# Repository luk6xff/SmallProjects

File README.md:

# SmallProjects
Here you can find some of my old tiny projects, code snippets, made for tests, fun or university which were created veeery long time ago :)

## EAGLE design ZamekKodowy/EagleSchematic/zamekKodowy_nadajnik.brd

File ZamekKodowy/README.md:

Digital wireless radio transmitter/receiver. TX consists of a 4x4 keyboard that can be used to type a PIN Code and then , the proper generated frame  is being sent to the specified receiver, All PIN codes are stored in non volatile EEPROM memory both in the transmiter and receiver. The device was made using STM32F051R8T6 microntroller , nRF24L01+ radio transceivers, AT24C64D eeprom memory . The entire system is powered by the FREERTOS

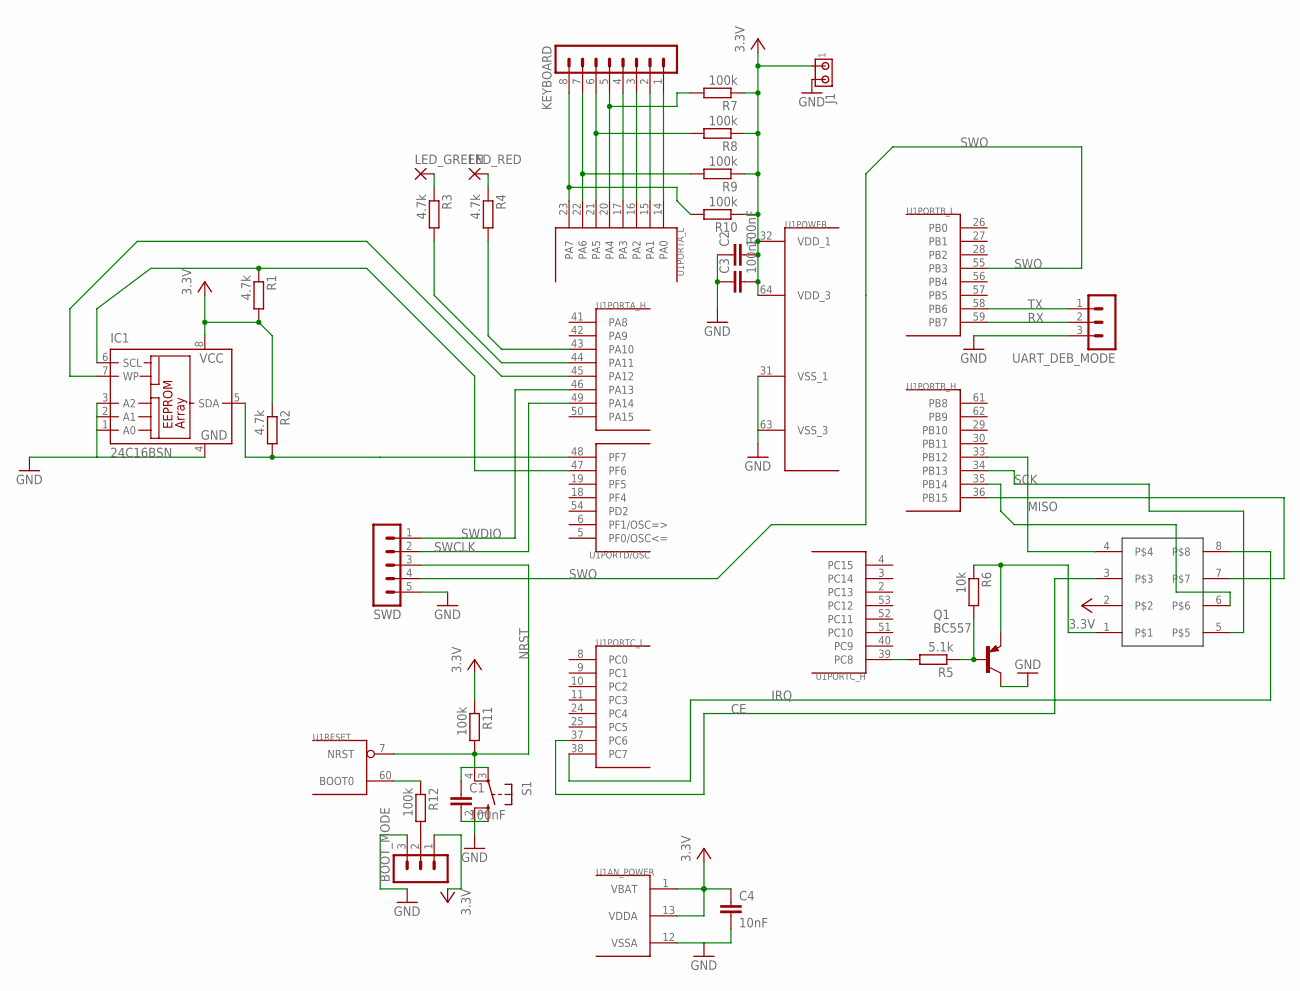
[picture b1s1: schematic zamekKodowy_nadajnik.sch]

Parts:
BOOT_MODE: MA03-1
C1, C2, C3: 100nF; C0603
C4: 10nF; C0603
CON1: CON10
IC1: 24C16BSN; SO-08
J1: MTA02-100; 10X02MTA
KEYBOARD: MA08-1
LED_GREEN: 2,54/0,9
LED_RED: 2,54/0,9
Q1: BC557; TO92
R1, R2, R3, R4: 4.7k; R0603
R5: 5.1k; R0603
R6: 10k; R0603
R7, R8, R9, R10, R11, R12: 100k; R0603
S1: 10-XX; B3F-10XX
SWD: MA05-1
U1: STM32F10XRXT6; TQFP64
UART_DEB_MODE: MA03-1

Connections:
CE: CON1.3, U1.37 (PC6)
GND: BOOT_MODE.3, C1.2, C2.1, C3.1, C4.2, IC1.1 (A0), IC1.2 (A1), IC1.3 (A2), IC1.4 (GND), J1.2, Q1.3 (C), S1.1 (S), S1.2 (S1), SWD.5, U1.12 (VSSA), U1.31 (VSS_1), U1.63 (VSS_3), UART_DEB_MODE.3
IRQ: CON1.8, U1.38 (PC7)
MISO: CON1.7, U1.36 (PB15)
MOSI: CON1.6, U1.35 (PB14)
unnamed: IC1.5 (SDA), R2.2, U1.48 (PF7)
unnamed: IC1.6 (SCL), R1.1, U1.47 (PF6)
unnamed: IC1.7 (WP), U1.45 (PA12)
unnamed: R3.2, U1.44 (PA11)
unnamed: R4.2, U1.43 (PA10)
unnamed: LED_GREEN.1, R3.1
unnamed: LED_RED.1, R4.1
unnamed: Q1.2 (B), R5.1, R6.2
unnamed: KEYBOARD.8, R10.2, U1.23 (PA7)
unnamed: R5.2, U1.39 (PC8)
unnamed: CON1.1, Q1.1 (E), R6.1
unnamed: KEYBOARD.7, R9.2, U1.22 (PA6)
unnamed: KEYBOARD.6, R8.2, U1.21 (PA5)
unnamed: KEYBOARD.5, R7.2, U1.20 (PA4)
unnamed: KEYBOARD.4, U1.17 (PA3)
unnamed: KEYBOARD.3, U1.16 (PA2)
unnamed: KEYBOARD.2, U1.15 (PA1)
unnamed: KEYBOARD.1, U1.14 (PA0)
unnamed: R12.1, U1.60 (BOOT0)
unnamed: BOOT_MODE.2, R12.2
NRST: C1.1, R11.2, S1.3, S1.4 (P1), SWD.3, U1.7 (NRST)
NSS: CON1.4, U1.33 (PB12)
RX: U1.59 (PB7), UART_DEB_MODE.2
SCK: CON1.5, U1.34 (PB13)
SWCLK: SWD.2, U1.49 (PA14)
SWDIO: SWD.1, U1.46 (PA13)
SWO: SWD.4, U1.55 (PB3)
TX: U1.58 (PB6), UART_DEB_MODE.1
VCC: BOOT_MODE.1, C2.2, C3.2, C4.1, CON1.2, IC1.8 (VCC), J1.1, R1.2, R2.1, R7.1, R8.1, R9.1, R10.1, R11.1, U1.1 (VBAT), U1.13 (VDDA), U1.32 (VDD_1), U1.64 (VDD_3)

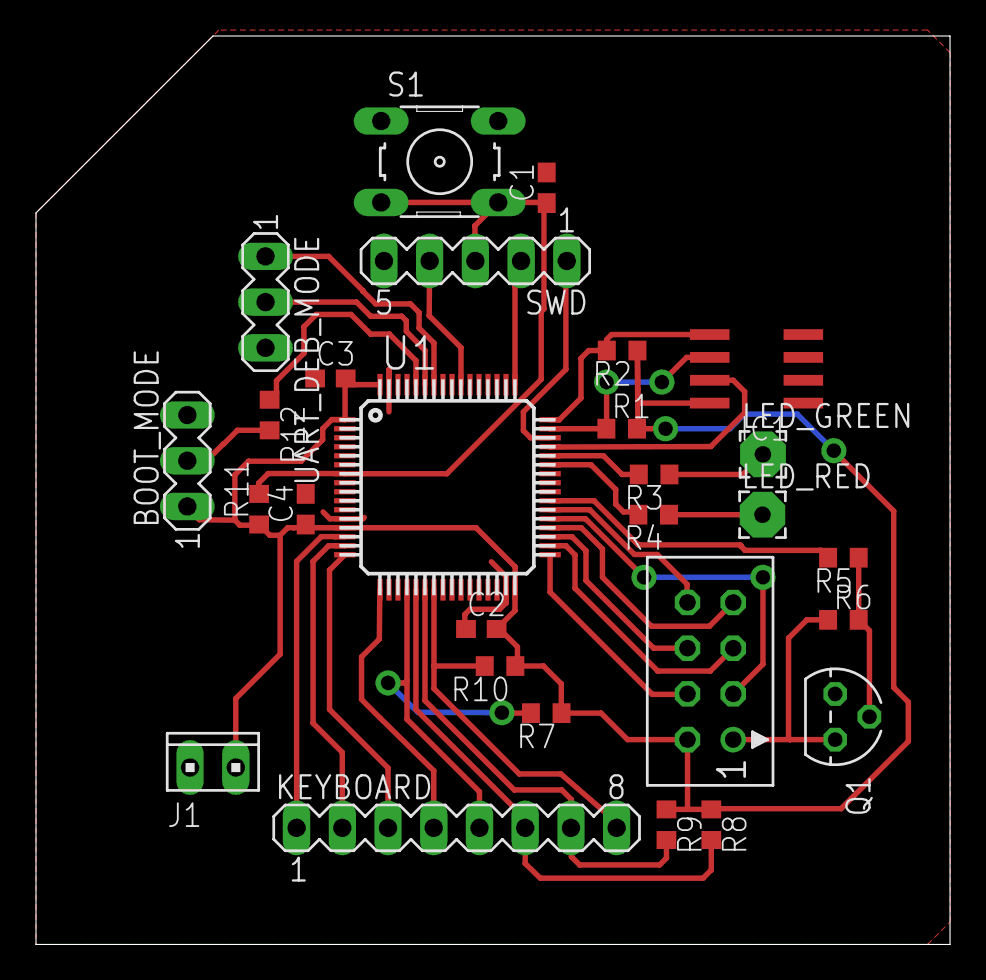
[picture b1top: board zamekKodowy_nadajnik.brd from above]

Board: 2 copper layers, 50.8 x 50.5 mm, 28 parts (0 on the bottom side), 34 nets.

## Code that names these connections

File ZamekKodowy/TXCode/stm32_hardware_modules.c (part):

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/**
 *@name void SPI2_For_NRF24L01_init(void)
 *@brief Initialization of the required SPI2 module registers
 *@brief PINOUT:  PB12(SPI2_NSS),  PB13(SPI2_SCK),  PB14(SPI2_MISO),  PB15(SPI2_MOSI)
 *@param NONE
 *@retval NONE
 *
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// GPIO
	//SetEnabledNRF24L01();
	GPIOB->MODER |= GPIO_MODER_MODER13_1 | GPIO_MODER_MODER14_1
			| GPIO_MODER_MODER15_1; // PB13(SPI2_SCK) , PB14(SPI2_MISO) , PB15(SPI2_MOSI) -> alternate function

	CS_PORT_SPI2->MODER |= CS_PIN_SPI2(GPIO_MODER_MODER,_0); //PB12(SPI2_NSS (CS) ) // OUTPUT
	CS_PORT_SPI2->PUPDR |= CS_PIN_SPI2(GPIO_PUPDR_PUPDR,_0); // PULL-UP

	CE_PORT_FOR_nRF24L01->MODER |= CE_PIN(GPIO_MODER_MODER,_0)/*6_0*/; // PC6 (PIN_CE) - OUTPUT
	CE_PORT_FOR_nRF24L01->PUPDR |= CE_PIN(GPIO_PUPDR_PUPDR,_0); // PC6 (PIN_CE) - PULL_UP
	//TODO -> PC7 IRQ INPUT
//SPI -> fpclk/4 ; MSB first ; NSS software
	//SPI2->CR1 = SPI_CR1_BR_0 | SPI_CR1_MSTR | SPI_CR1_SSM;
	//-> 8bit ; fifo 8bit , tx/rx dma enabled // interrupts for TX and RX
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
	RCC_AHBPeriphClockCmd(RCC_AHBENR_GPIOCEN, ENABLE);
	RCC_APB2PeriphClockCmd(RCC_APB2ENR_SYSCFGEN, ENABLE); // Enable SYSCFG clock
	IRQ_PORT_FOR_nRF24L01->MODER &= ~(IRQ_PIN(GPIO_MODER_MODER,)); //PC7(IRQ ) // INPUT
	IRQ_PORT_FOR_nRF24L01->PUPDR |= IRQ_PIN(GPIO_PUPDR_PUPDR,_0); // PULL-UP
	SYSCFG_EXTILineConfig(EXTI_PortSourceForIRQ, EXTI_PinSourceForIRQ);
	EXTI->IMR |= EXTI_IMR_MR7; //Interrupt request from PC7 is not masked
	EXTI->FTSR |= EXTI_FTSR_TR7; // Falling trigger edge
	/*NVIC for EXTI enable	*/
	NVIC_SetPriority(EXTI4_15_IRQn, 4);
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////////////////////////////////////////////////////////////USART///////////////////////////////////////////////////////
/**
 * @name   static void USART1Init(void)
 * @brief  Configures USART2 com port. PB6 (USART1_TX) , PB7(USART1_RX)
 * @retval None
 */

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
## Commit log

2015-05-14 USB CDS echo example for EFM32 microcontrollers ver0.1
2015-07-23 zamek kodowy project added
2015-07-23 zamek kodowy project updated
2015-07-23 parts list added to zamek kodowy project
2015-07-23 zamekKodowy - repo reorganized
2015-07-23 entire repo updated
2015-07-23 font converter to 'C-like char table program added
2015-07-23 matlab code for a program to compute chain parameters of transformers added
2015-07-23 Vtk project to show features of contouring of shapes added
2015-11-01 Project using for simulating and testing our modular electronics
2015-11-01 Project using for simulating and testing our modular electronics added - created with mbed
2015-11-03 bug fixing in test demo app for sensors
2015-11-10 New version of app tester added, frame sizes changed
2015-11-12 Byte data write method implemented ,
2015-11-15 Complete test application prepared
2015-11-22 Null from end of frame removed
2015-12-20 ModularElectronics Sensor simulation project moved to the parent project
2016-02-16 Circullar Buffer implementation in java added
